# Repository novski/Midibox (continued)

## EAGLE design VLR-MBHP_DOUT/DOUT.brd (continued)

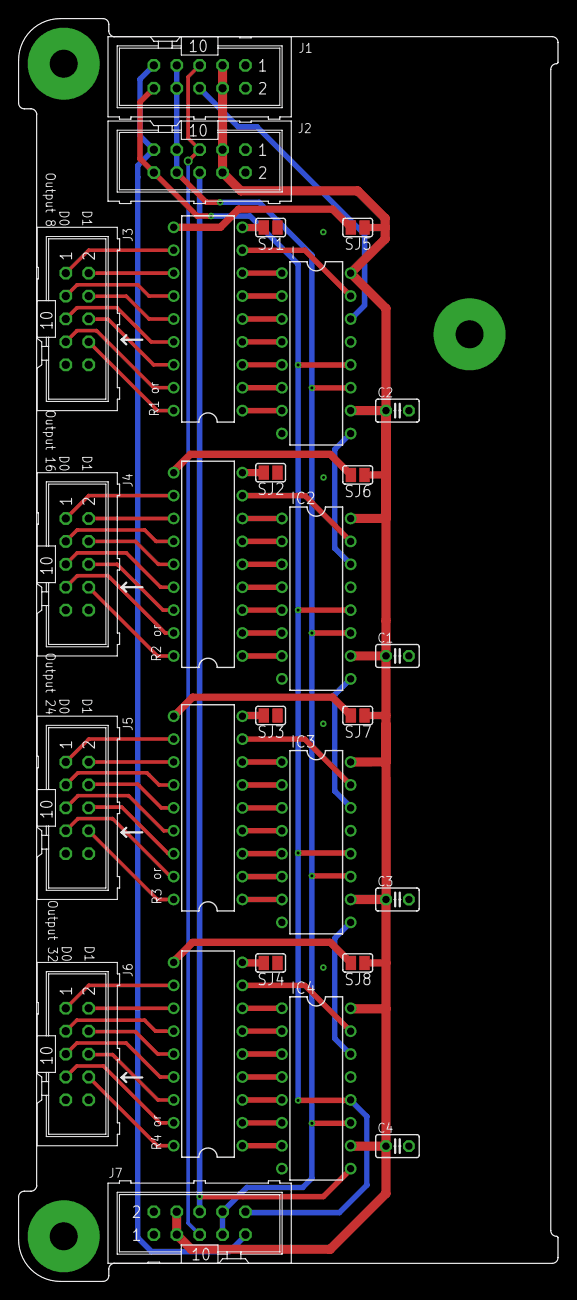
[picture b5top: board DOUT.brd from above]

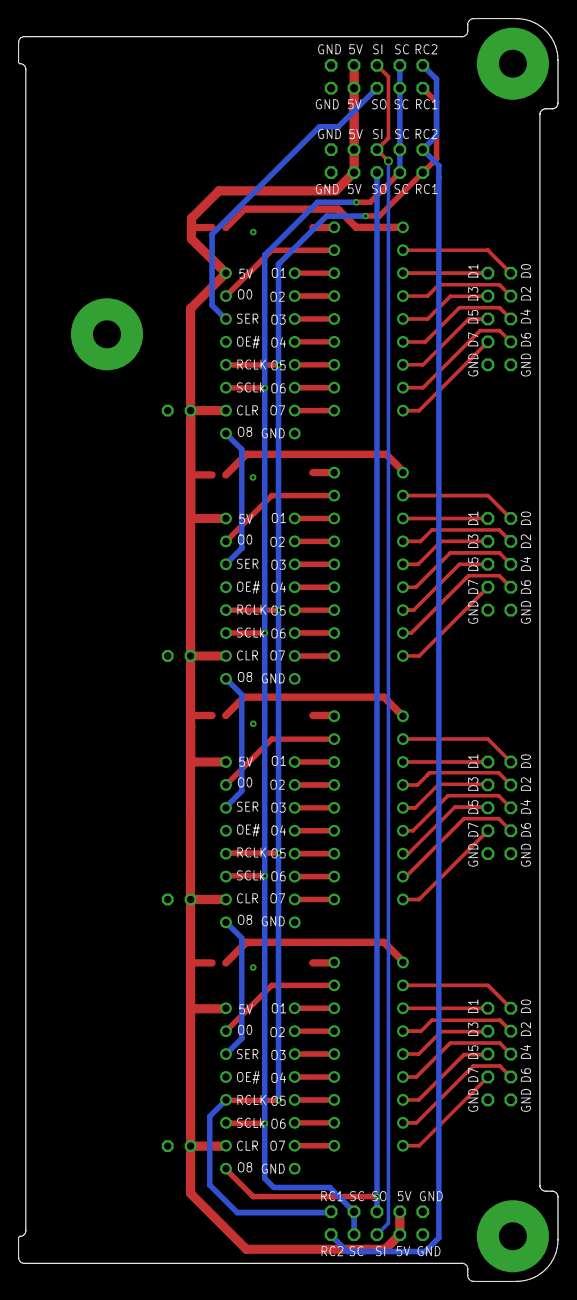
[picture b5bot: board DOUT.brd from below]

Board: 2 copper layers, 59.8 x 140.0 mm, 32 parts (2 on the bottom side), 83 nets.

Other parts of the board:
U$2, U$3: DOUT
U$4, U$5: VLRLAB
